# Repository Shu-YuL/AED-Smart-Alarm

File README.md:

# AED Smart Alarm

--updated Jan 17, 2023 by Shu-Yu Lin

--updated Feb 14, 2023 by Shu-Yu Lin

--updated Mar 14, 2023 by Shu-Yu Lin

--updated Mar 27, 2023 by Shu-Yu Lin

--updated Apr 4, 2023 by Shu-Yu Lin

--updated Apr 30, 2023 by Shu-Yu Lin

----------------------------------------------------------------

## Demo Video

[![Demo Video](https://lh3.googleusercontent.com/fife/APg5EOZy0qmSeqRbGbYMGeu49TxH5lmIOj3HhFyADLr6qH4S8TAaIJzbBPQnfgN_s-cPjZGFoLVAi6fIpvv_eCJc7_dvCM5OVtgkbksEu1INZQIVRCa6F0s9MO7LJb4W_VmwPlCb04PSN6UpbPwQ0xZxmr8z40CDwzgnBYsCoBz82gxHBdwRRx3AK6PTTbE4swi1r4OC8VxJj83QZSaBq_axB13bFNfvSjfkM9lRGnLXVgempMBgW_JMlQ8JZupSTVby1mXDgkiXalZTfnvae9LtgSR2kD4ZaaPTBrLYbnSjJoOcwekloa4i9upgvwhmV6UuGPqelpdEVIKUb0zCZGPnMjvvsTw_2Po14uoSeGETeqKRDd6uW2YArJD77ucuMG6qNt2Gem0yAI9NxQhCjbwBNYsCyjXGaa2BgXaY-8XdDqX1Mx07VmGnCa4fYvGSmAh2E12dP3vBXci5WtxpB1mUBuGlYkXIpvd327HO3nS2LpaJxP5piBP93a9GQkfz6OSpcxceiy6YWZIpN3cmGjMtxCaoLY8ixNX4d9ixSc4fpJpaSr7I3dkZImk0GOwjqR3xibleN_GsKG0moCss992vfX2BKf0Jc9spBMjNV6-2EfTBknmBre45v9of6kBL2GSb3d6iRzKlJ31yBRbIjqMMEWdltXHwqPHpjVWfJihoVlNe3wC1QZjWhIwFi8nv6nqt33q25jnV4J3Cq5mtlX1iGLJC8Z48cVMwxL9PpYGNN1b59B_K5U_RwdsI4gLgNnz999uuzSIeae5vx8KiVRm7SkXUUmuWnSZf90uaKBqZnekPYPGBeCjfYeUKWx3TFvJ6D0dil_QGtLUs6PXrIOAVoQ4H-kTlWyh0TMBW9p63Tly5B2JojbUkzhm8_w84FCkqoo5ElOnNsiUPa9Vcq175EdBHcfhmW7sAL8E7n9_DCXVNkeGwU5FgteWTIfNH1ESyxW_-bmufeuZ6pC-AliJgboJIaW5ZRdk58-B8PeqJ1hRr_7eFB8cpDLPJBaY8Vsg7hvgu3LZmLCbm73OjMXCEUkPtxawnfU5iJiKNJTYGJsBCpuVoUwR9EyLYlWgCaQFeHb-f_gmBUNcvSdV69-jib-mk7-MQOCFCYeSE1sNLpaVtzJmPjppp7XQHR8aCpdl6hikow4ChZ8Y4b8jt7gqkqRCYXpGSENUku35SLy19q8GuZnQ4OqCBEZjhRtRddLTxCOrBvjnOxRmyqougyYPEXUmoWOx0TKGyY6Hjho5ErniS5xrw8hKajbjSjN2OwMH83XZyLO3kg3vtkb_LYo6-RBT3pzAC8Ps_SLnvr4ILTwVZnF5t3VGGtdLRFFjI0h4WdgBgli0Bb7BPlsqJt8sOZdLPsWhUT5cgD280GumtA7FQvgNvclBMwaH1jCS99OAF7J4bOnOJqg_cTY4eNW_orggrD6oAf2BFiCVVzpNTNuUOSClDvBvviMVxwNR2MIcZnvopvAHA721Vph1cjg38kVMJq1Zw_ECSs386fh8K1YeYqixkRFTugn3-30Zh77XmVHoywLTSx9y_oey-ck5fwWFaPlW8vO2vpDeKGk-cMl2PZALwcuiQga5bR0iar3lV_XzlYYY=w1920-h1080-k-pd)](https://drive.google.com/file/d/1JeJAB9AQrucV8XEORTZ0Mz8k3fBR3jVF/view?usp=sharing "Demo video")

## Introduction

Our project aims to improve upon the current AED monitoring system used by the University of Alberta Emergency Management Team (UAEMT) and University of Alberta Protective Services (UAPS). The current system has issues with delays in receiving alerts and the need for frequent re-authentication. Our new system addresses these issues and provides more advanced notice for time-sensitive alerts, enabling UAPS to respond more quickly in case of a medical emergency.

## Method of Project Approach

Our project consists of three main components. The first component is the alarm, a monitoring device installed inside each AED cabinet and used to detect if the cabinet door opens. The second component is a base station unit installed inside the UAPS office used notify people in the office if any of the alarm monitoring devices inside the AED cabinet are triggered. The third component is a Google Apps Script managed Google Sheets, it processes HTTP requests sent from the base station and the monitoring devices and sends **an email, along	with Telegram and Discord channel announcement message** to UAPS if any of the monitoring devices are triggered.

### Monitoring Device

- Every monitoring device is powered by batteries.
- A door switch sensor is used to detect any motion of the cabinet door.
- The activation of the switch sends a digital signal to wake up and trigger the device.
- The development board used is ESP32-DevKitC V4.
- When the MCU is active, it will try to connect to campus WiFi and sends its MAC address to the Google Sheet through an HTTP GET request.
- The monitoring device will go back to sleep after it receives an acknowledgement from the Google Sheet.

### Base Station

- The base station is powered by a wall outlet power supply that will supply 5V.
- The MCU used for the base station is ESP32-WROOM-32E.
- An 2004 LCD display is mounted on the base station and connected to the MCU via the I²C interface.
- LED bulbs are used and controlled via the MCU's digital output signal. Similarly, a piezoelectric buzzer is also used and controlled via PWM signals from the MCU.
- The base station is to be connected to campus Wifi and pull data from the Google Sheet every 10 seconds through sending an HTTP GET request. It receives an empty message when no monitoring device is triggered. If any of the monitoring devices are triggered, it receives a string showing the location of this monitoring device and then activates buzzer, LED, and also displays alert message on the LCD display.
- Users can interact with the base station with onboard pushbuttons. One pushbutton labeled "Clear" is used to dismiss an alert event, while the other one is used to turn off the buzzer.

### Google Sheet

- Serves as a Web Server and online User Interface for the project
- Manages HTTP Requests and data sent from both the Base Station and the Monitoring Devices
- Provides an paired device list that can be managed by the user
- Provides an Event Log sheet that records all triggering events along with triggered date and time of each event
- Sends notifications through email, Telegram and Discord channel when an event is triggered or cleared
- Sends notifications through email, Telegram and Discord channel when a prospect low battery is detected

The project firmware is developed in C language using ESP-IDF. The Google Sheet is managed using Google Apps Script which the script is developed in JavaScript.

## Usage of this Repository

This repository contains all the code, files such as the hardware design project, PCB layout and 3D models. Please refer to the documentation for instructions on how to set up and use the system.

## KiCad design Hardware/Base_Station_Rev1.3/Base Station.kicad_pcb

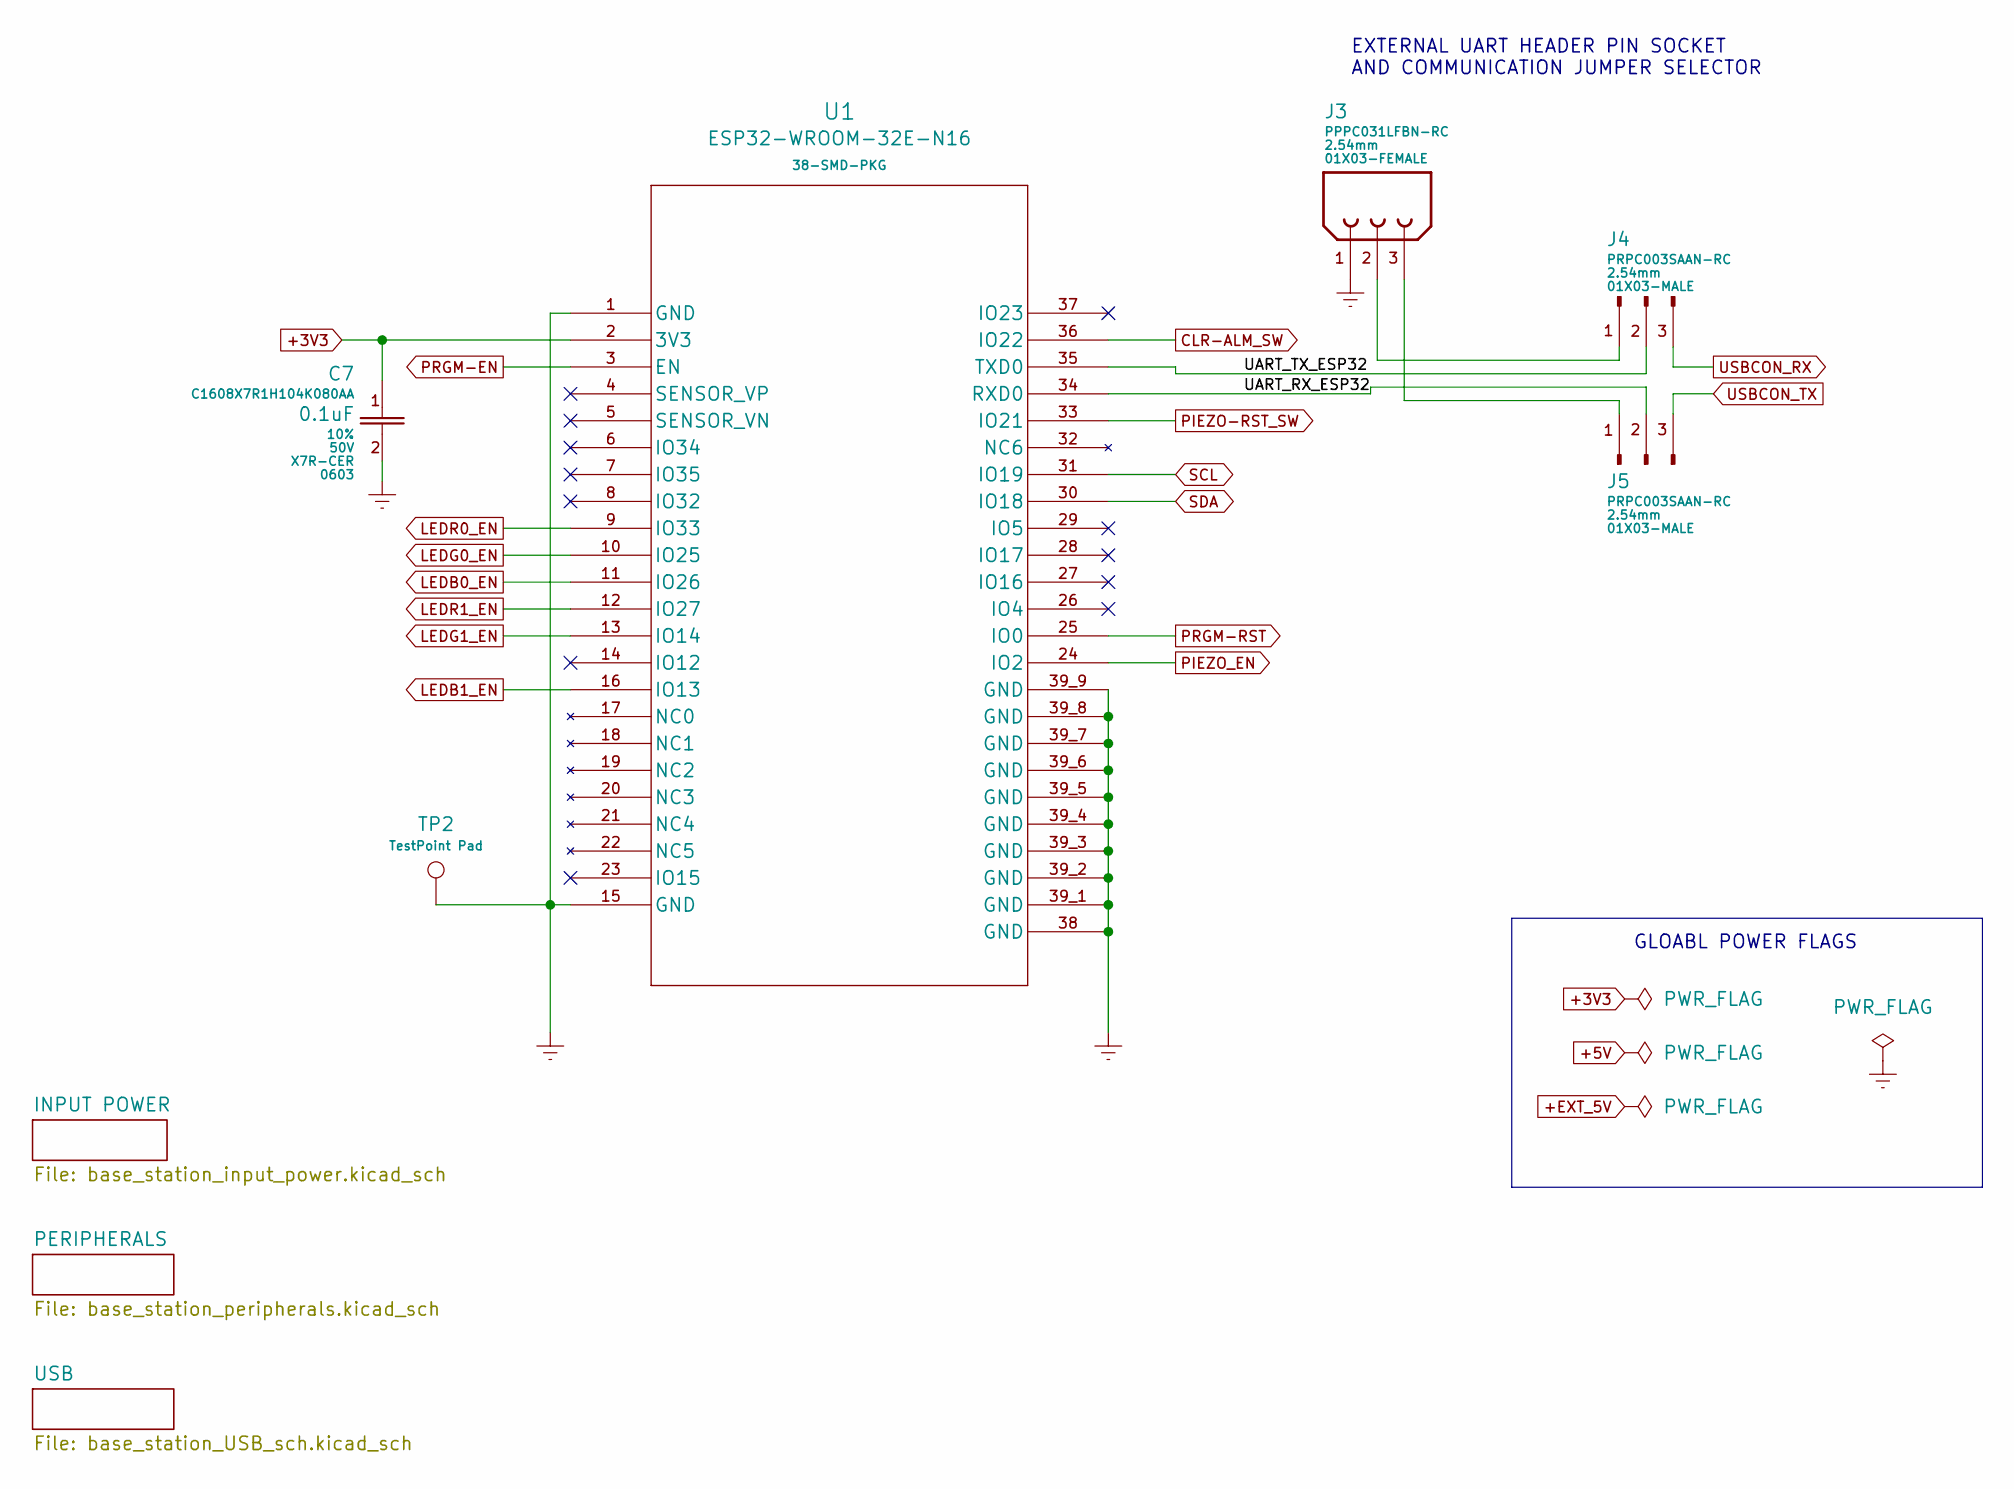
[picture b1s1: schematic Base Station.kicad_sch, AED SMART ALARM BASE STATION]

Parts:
C7: C1608X7R1H104K080AA; Tolerance 10%; Rated Voltage 50V
J3: PPPC031LFBN-RC
J4, J5: PRPC003SAAN-RC
TP2: TestPoint Pad; TestPoint_Pad_1.0x1.0mm
U1: ESP32-WROOM-32E-N16

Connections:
+3V3: C7.1, U1.2 (3V3); also elsewhere on the board
/UART_RX_ESP32: J5.2, U1.34 (RXD0)
/UART_TX_ESP32: J4.2, U1.35 (TXD0)
CLR-ALM_SW: U1.36 (IO22); also elsewhere on the board
Earth: C7.2, J3.1, TP2.1, U1.1 (GND), U1.15 (GND), U1.38 (GND), U1.39_1 (GND), U1.39_2 (GND), U1.39_3 (GND), U1.39_4 (GND), U1.39_5 (GND), U1.39_6 (GND), U1.39_7 (GND), U1.39_8 (GND), U1.39_9 (GND); also elsewhere on the board
LEDB0_EN: U1.11 (IO26); also elsewhere on the board
LEDB1_EN: U1.16 (IO13); also elsewhere on the board
LEDG0_EN: U1.10 (IO25); also elsewhere on the board
LEDG1_EN: U1.13 (IO14); also elsewhere on the board
LEDR0_EN: U1.9 (IO33); also elsewhere on the board
LEDR1_EN: U1.12 (IO27); also elsewhere on the board
unnamed: J3.2, J4.1
unnamed: J3.3, J5.1
PIEZO-RST_SW: U1.33 (IO21); also elsewhere on the board
PIEZO_EN: U1.24 (IO2); also elsewhere on the board
PRGM-EN: U1.3 (EN); also elsewhere on the board
PRGM-RST: U1.25 (IO0); also elsewhere on the board
SCL: U1.31 (IO19); also elsewhere on the board
SDA: U1.30 (IO18); also elsewhere on the board
USBCON_RX: J4.3; also elsewhere on the board
USBCON_TX: J5.3; also elsewhere on the board

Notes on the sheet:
GLOABL POWER FLAGS
EXTERNAL UART HEADER PIN SOCKET AND COMMUNICATION JUMPER SELECTOR

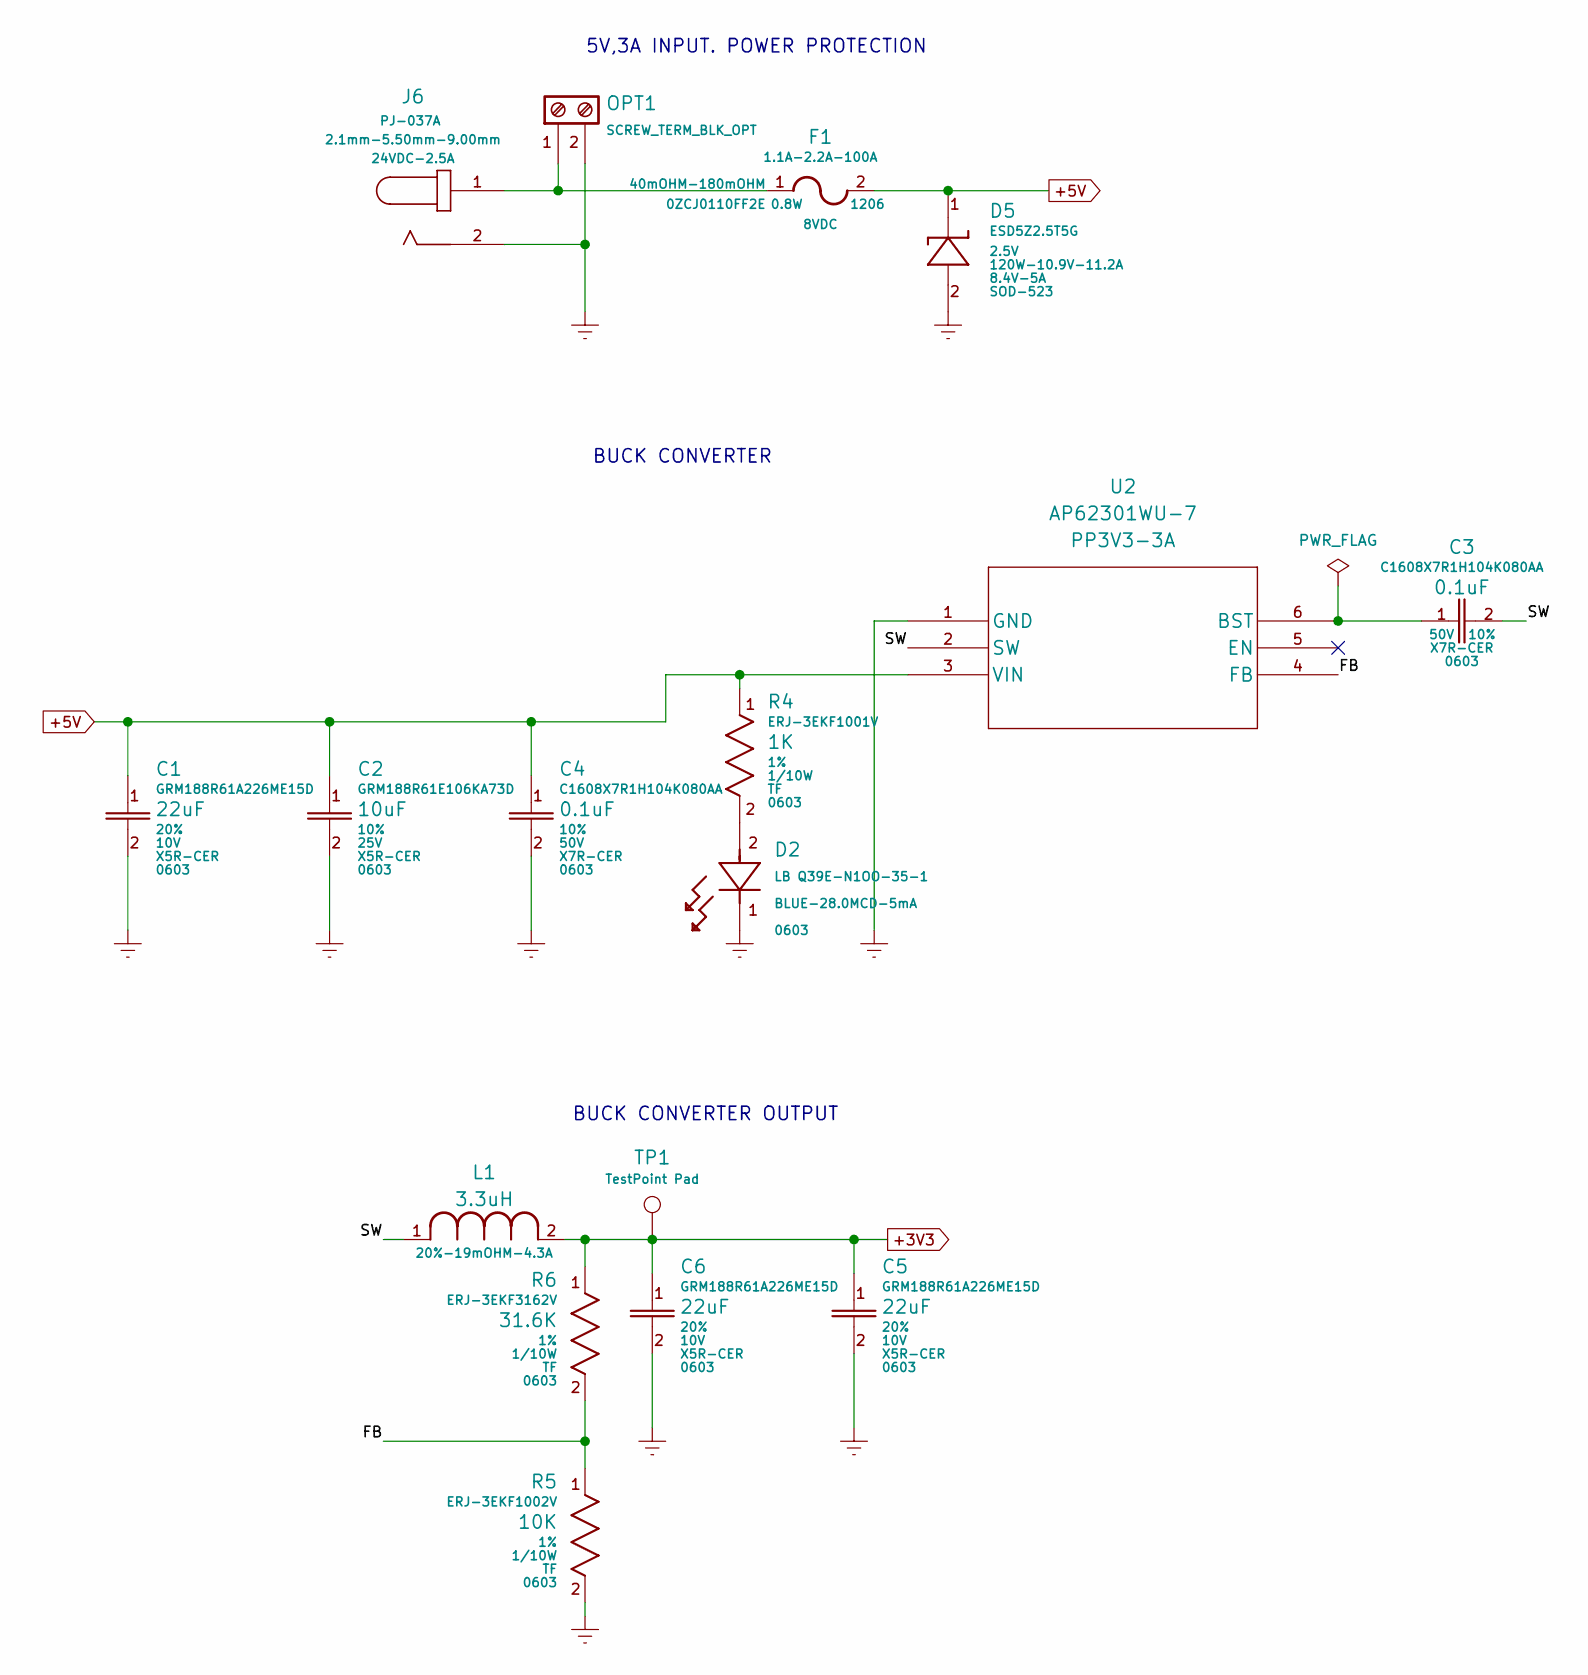
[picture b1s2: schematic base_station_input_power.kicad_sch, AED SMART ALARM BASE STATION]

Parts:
C1, C5, C6: GRM188R61A226ME15D; Tolerance 20%; Rated Voltage 10V
C2: GRM188R61E106KA73D; Tolerance 10%; Rated Voltage 25V
C3, C4: C1608X7R1H104K080AA; Tolerance 10%; Rated Voltage 50V
D2: LB Q39E-N1OO-35-1
D5: ESD5Z2.5T5G; Clamping Voltage 8.4V-5A
F1: 0ZCJ0110FF2E; Max Voltage 8VDC
J6: PJ-037A; Rating 24VDC-2.5A
L1: NRS8030T3R3MJGJ; Tolerance + DCR + Rated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 20%-19mOHM-4.3A
OPT1: SCREW_TERM_BLK_OPT; CUI_TB002-500-02BE
R4: ERJ-3EKF1001V; Tolerance 1%
R5: ERJ-3EKF1002V; Tolerance 1%
R6: ERJ-3EKF3162V; Tolerance 1%
TP1: TestPoint Pad; TestPoint_Pad_1.0x1.0mm
U2: AP62301WU-7

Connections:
+3V3: C5.1, C6.1, L1.2, R6.1, TP1.1; also elsewhere on the board
+5V: C1.1, C2.1, C4.1, D5.1 (C), F1.2, R4.1, U2.3 (VIN); also elsewhere on the board
/INPUT POWER/FB: R5.1, R6.2, U2.4 (FB)
/INPUT POWER/SW: C3.2, L1.1, U2.2 (SW)
Earth: C1.2, C2.2, C4.2, C5.2, C6.2, D2.1, D5.2 (A), J6.2, OPT1.2 (GND), R5.2, U2.1 (GND); also elsewhere on the board
unnamed: C3.1, U2.6 (BST)
unnamed: D2.2, R4.2
unnamed: F1.1, J6.1, OPT1.1 (5V)

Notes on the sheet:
BUCK CONVERTER OUTPUT
BUCK CONVERTER
5V,3A INPUT. POWER PROTECTION

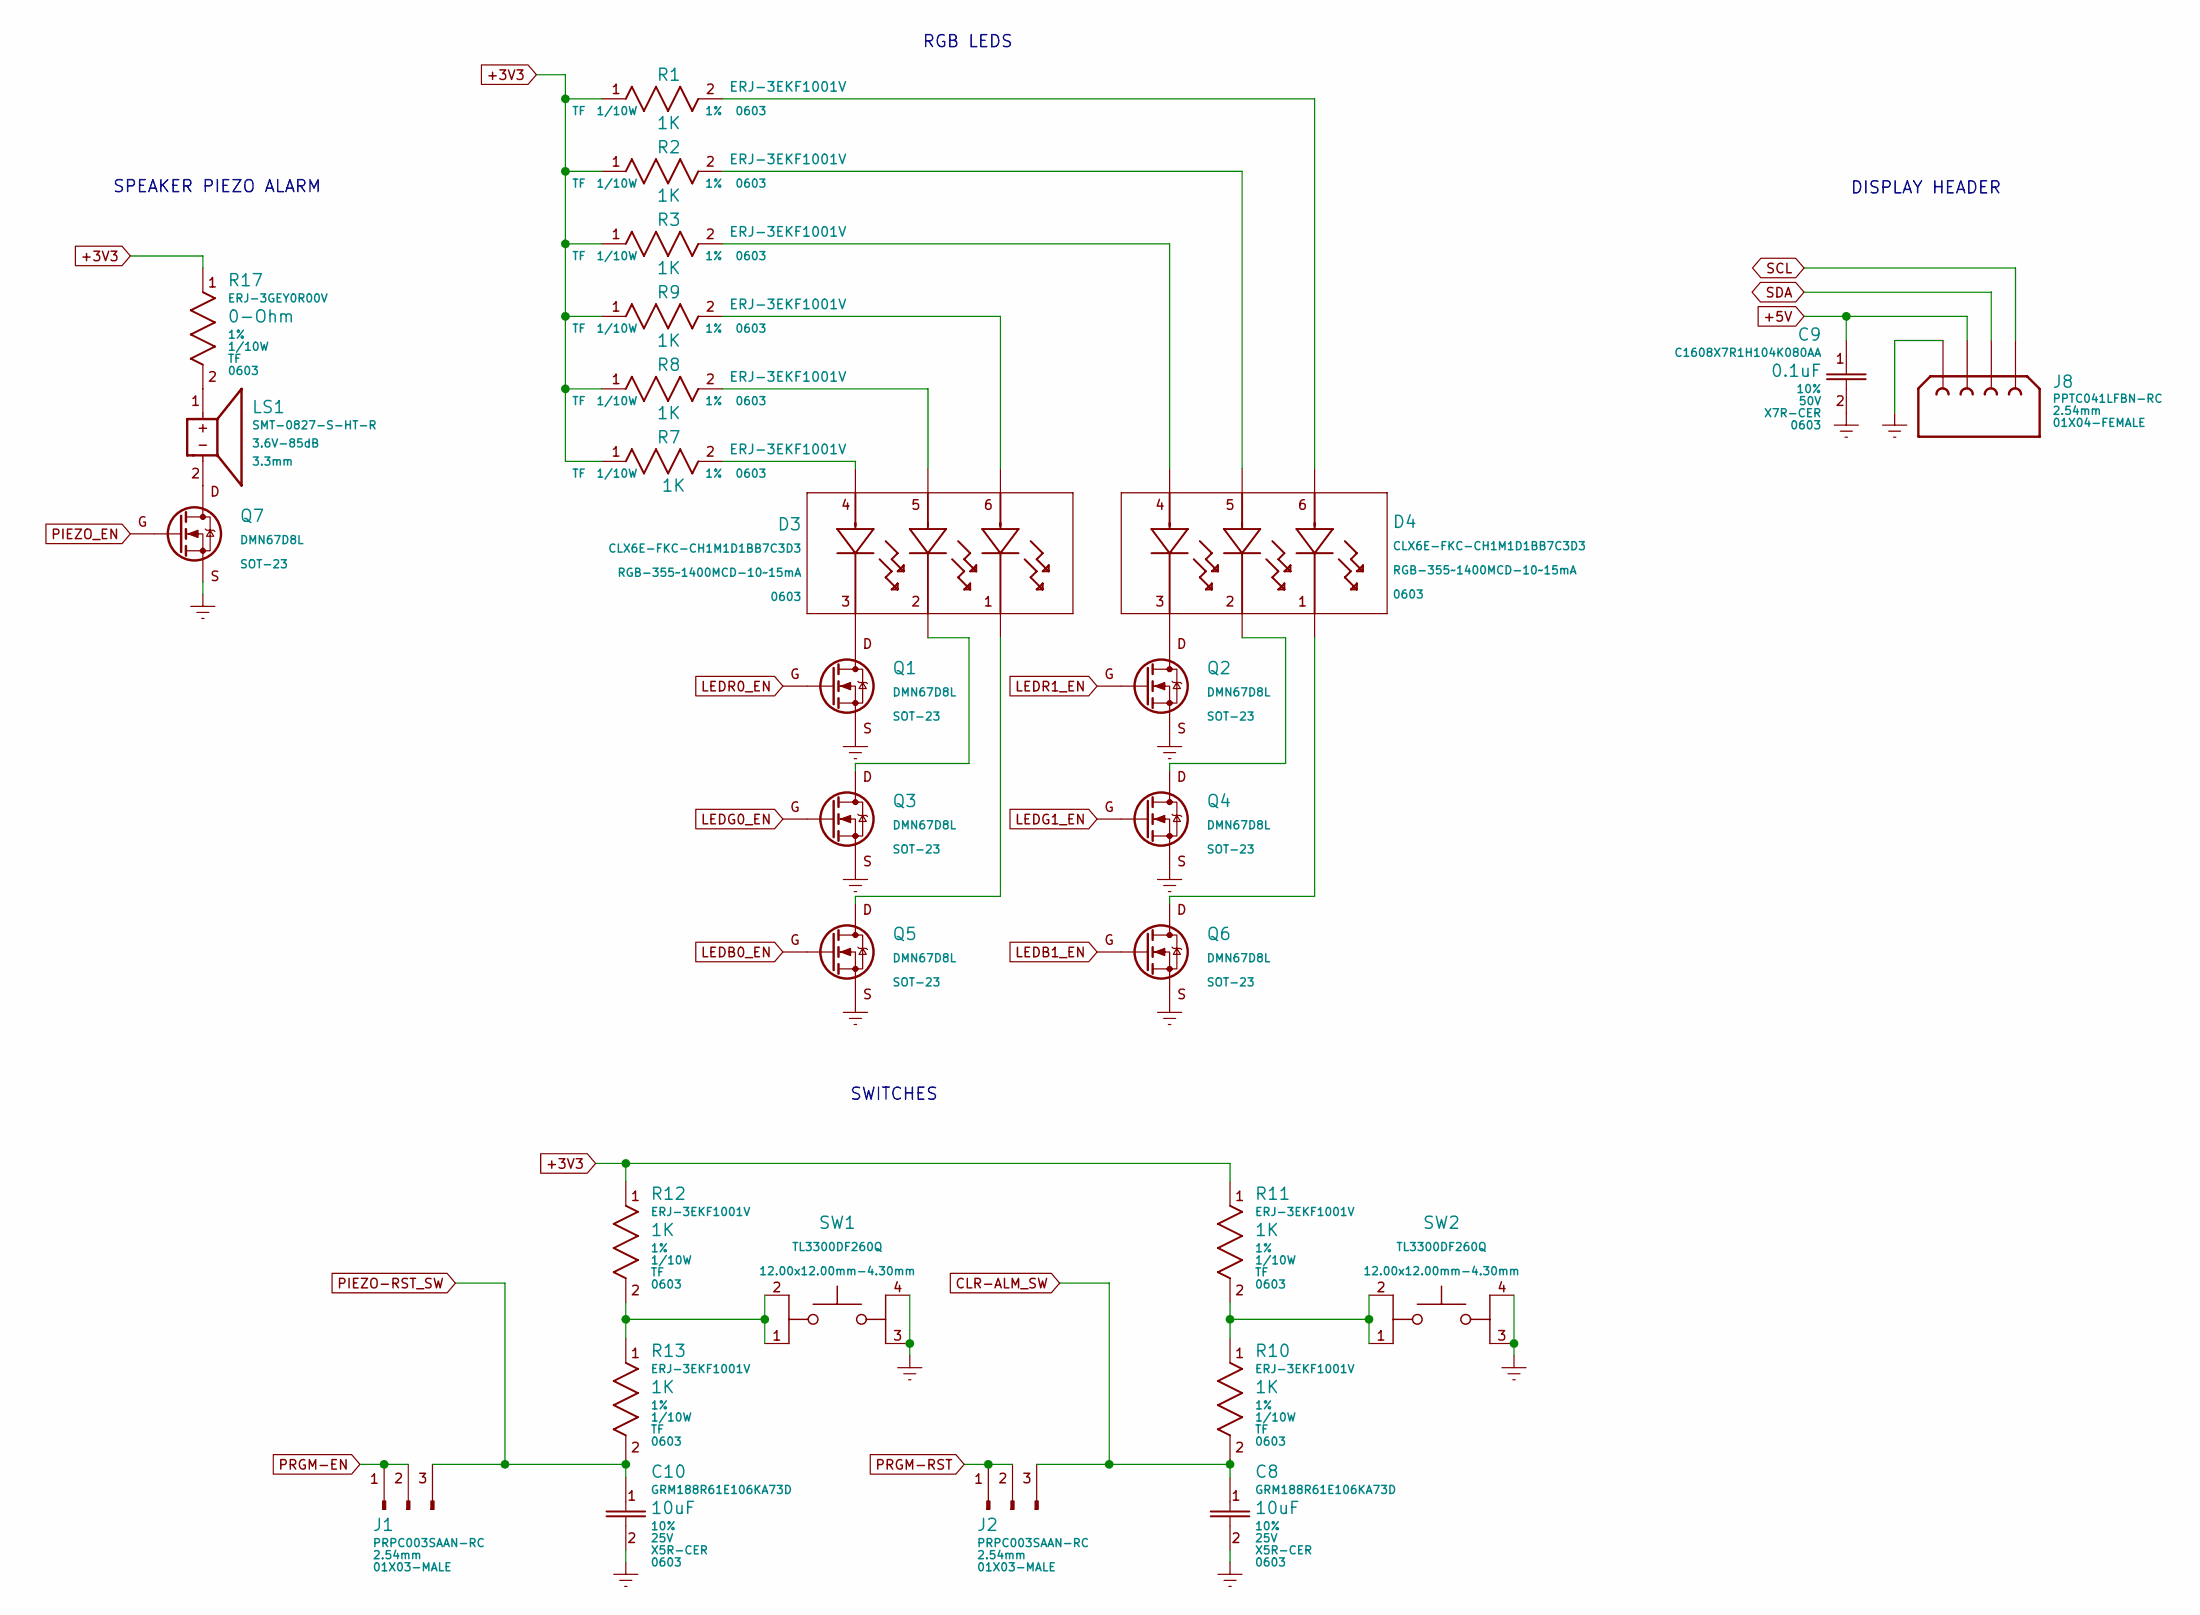
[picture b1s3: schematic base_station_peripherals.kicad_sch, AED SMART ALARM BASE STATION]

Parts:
C8, C10: GRM188R61E106KA73D; Tolerance 10%; Rated Voltage 25V
C9: C1608X7R1H104K080AA; Tolerance 10%; Rated Voltage 50V
D3, D4: CLX6E-FKC-CH1M1D1BB7C3D3
J1, J2: PRPC003SAAN-RC
J8: PPTC041LFBN-RC; PARTREV J - 04/15/2015
LS1: SMT-0827-S-HT-R; Voltage-Sound Pressure 3.6V-85dB; Part Revision 31/03/20
Q1, Q2, Q3, Q4, Q5, Q6, Q7: DMN67D8L; DMN67D8L-7
R1, R2, R3, R7, R8, R9, R10, R11, R12, R13: ERJ-3EKF1001V; Tolerance 1%
R17: ERJ-3GEY0R00V; Tolerance 1%
SW1, SW2: TL3300DF260Q; PARTREV A

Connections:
+3V3: R1.1, R2.1, R3.1, R7.1, R8.1, R9.1, R11.1, R12.1, R17.1; also elsewhere on the board
+5V: C9.1, J8.2; also elsewhere on the board
CLR-ALM_SW: C8.1, J2.3, R10.2; also elsewhere on the board
Earth: C8.2, C9.2, C10.2, J8.1, Q1.2 (S), Q2.2 (S), Q3.2 (S), Q4.2 (S), Q5.2 (S), Q6.2 (S), Q7.2 (S), SW1.3, SW1.4, SW2.3, SW2.4; also elsewhere on the board
LEDB0_EN: Q5.1 (G); also elsewhere on the board
LEDB1_EN: Q6.1 (G); also elsewhere on the board
LEDG0_EN: Q3.1 (G); also elsewhere on the board
LEDG1_EN: Q4.1 (G); also elsewhere on the board
LEDR0_EN: Q1.1 (G); also elsewhere on the board
LEDR1_EN: Q2.1 (G); also elsewhere on the board
unnamed: D3.1, Q5.3 (D)
unnamed: D3.2, Q3.3 (D)
unnamed: D3.3, Q1.3 (D)
unnamed: D3.4, R7.2
unnamed: D3.5, R8.2
unnamed: D3.6, R9.2
unnamed: D4.1, Q6.3 (D)
unnamed: D4.2, Q4.3 (D)
unnamed: D4.3, Q2.3 (D)
unnamed: D4.4, R3.2
unnamed: D4.5, R2.2
unnamed: D4.6, R1.2
unnamed: LS1.1 (+), R17.2
unnamed: LS1.2 (-), Q7.3 (D)
unnamed: R10.1, R11.2, SW2.1, SW2.2
unnamed: R12.2, R13.1, SW1.1, SW1.2
PIEZO-RST_SW: C10.1, J1.3, R13.2; also elsewhere on the board
PIEZO_EN: Q7.1 (G); also elsewhere on the board
PRGM-EN: J1.1, J1.2; also elsewhere on the board
PRGM-RST: J2.1, J2.2; also elsewhere on the board
SCL: J8.4; also elsewhere on the board
SDA: J8.3; also elsewhere on the board

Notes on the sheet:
SWITCHES
RGB LEDS
SPEAKER PIEZO ALARM
DISPLAY HEADER

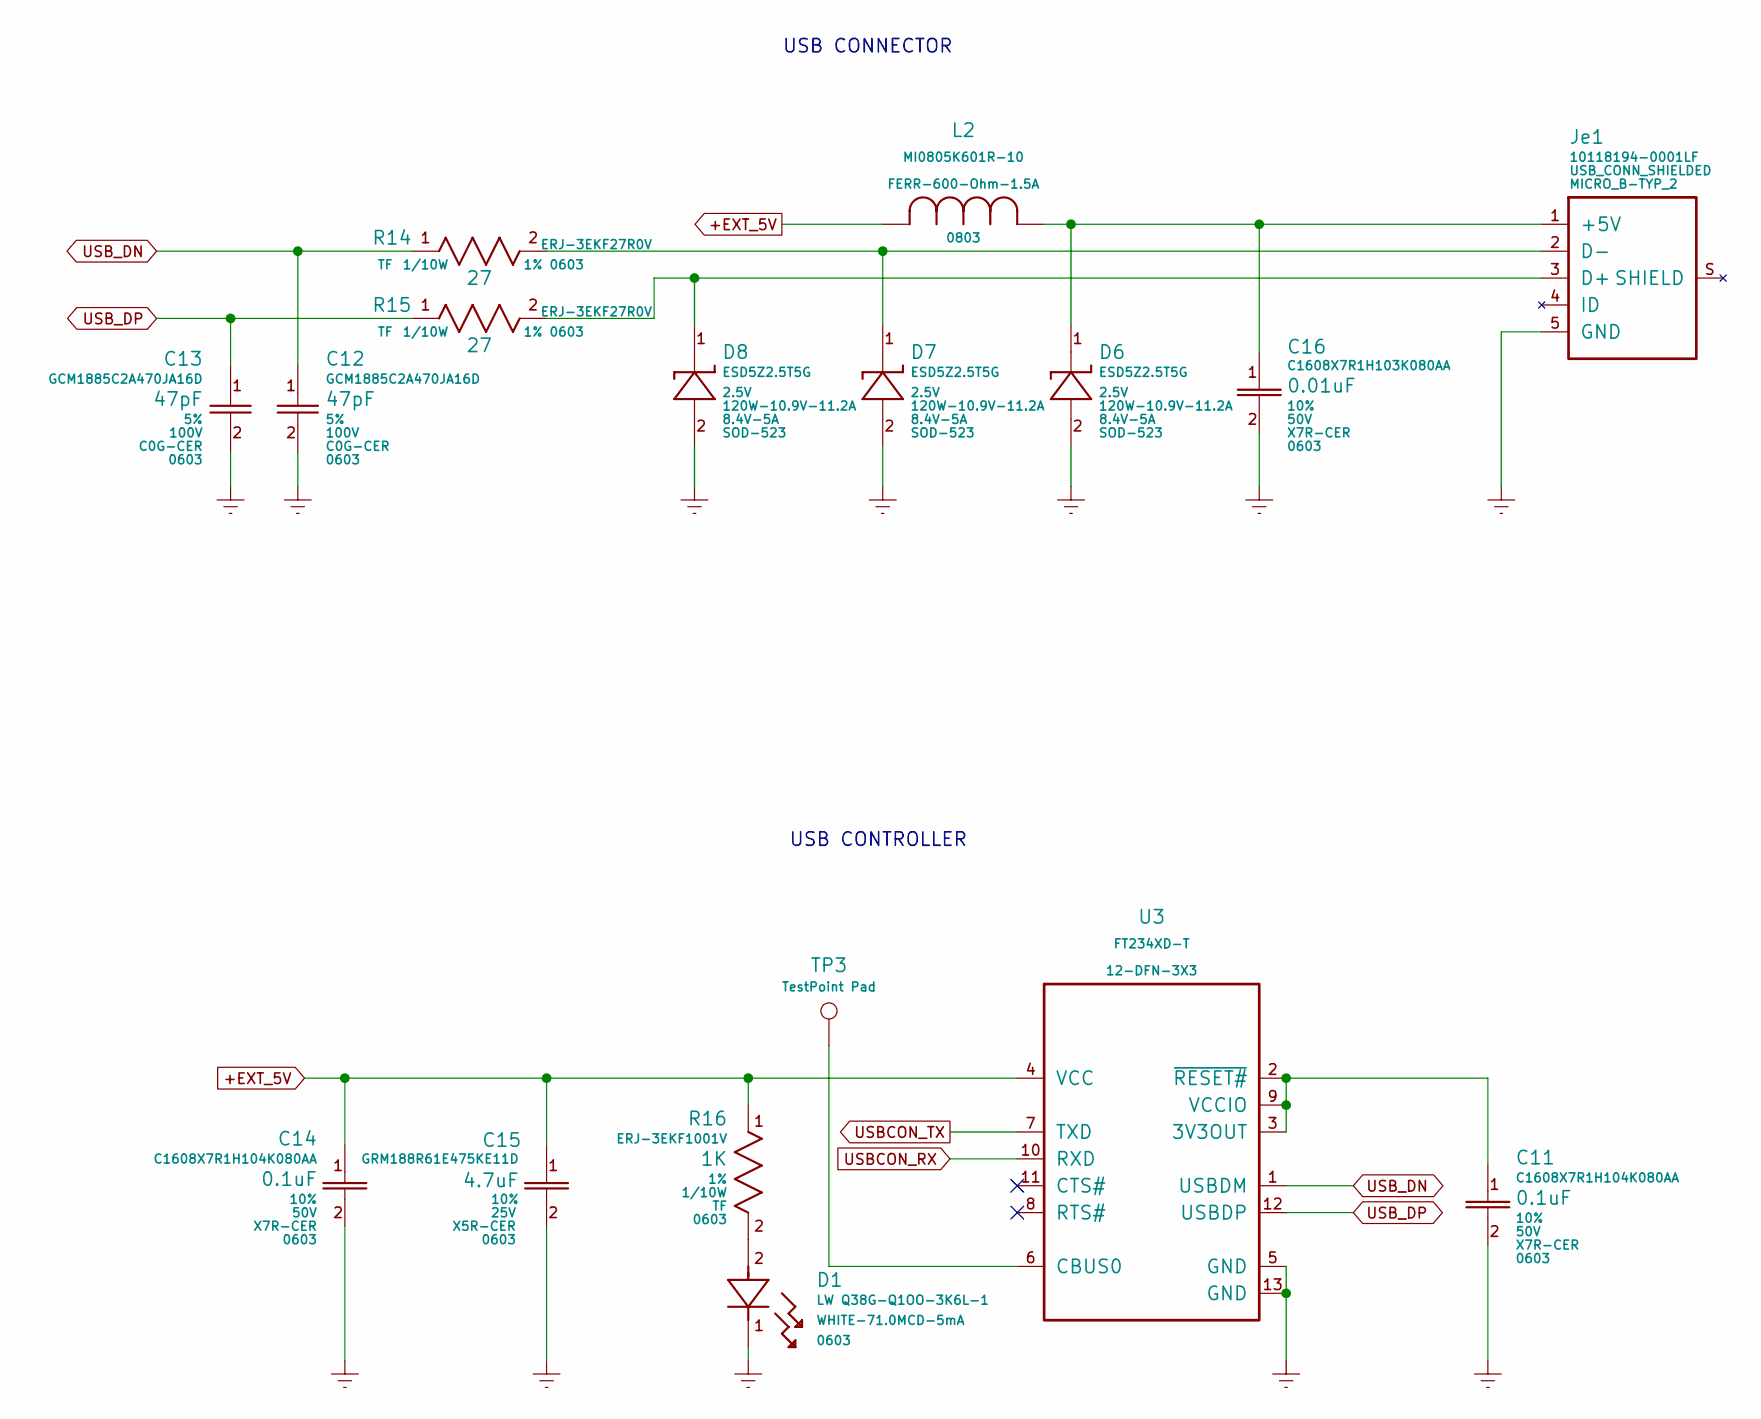
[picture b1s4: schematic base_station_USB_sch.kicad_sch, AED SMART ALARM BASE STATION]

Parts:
C11, C14: C1608X7R1H104K080AA; Tolerance 10%; Rated Voltage 50V
C12, C13: GCM1885C2A470JA16D; Tolerance 5%; Rated Voltage 100V
C15: GRM188R61E475KE11D; Tolerance 10%; Rated Voltage 25V
C16: C1608X7R1H103K080AA; Rated Voltage 50V; Tolerance 10%
D1: LW Q38G-Q1OO-3K6L-1
D6, D7, D8: ESD5Z2.5T5G; Clamping Voltage 8.4V-5A
Je1: 10118194-0001LF
L2: MI0805K601R-10
R14, R15: ERJ-3EKF27R0V; ERJ3EKF27R0V; Tolerance 1%
R16: ERJ-3EKF1001V; Tolerance 1%
TP3: TestPoint Pad; TestPoint_Pad_1.0x1.0mm
U3: FT234XD-T

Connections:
+EXT_5V: C14.1, C15.1, L2.1, R16.1, U3.4 (VCC)
Earth: C11.2, C12.2, C13.2, C14.2, C15.2, C16.2, D1.1, D6.2 (A), D7.2 (A), D8.2 (A), Je1.5 (GND), U3.5 (GND), U3.13 (GND); also elsewhere on the board
unnamed: C11.1, U3.2 (~RESET#), U3.3 (3V3OUT), U3.9 (VCCIO)
unnamed: C16.1, D6.1 (C), Je1.1 (+5V), L2.2
unnamed: D1.2, R16.2
unnamed: D7.1 (C), Je1.2 (D-), R14.2
unnamed: D8.1 (C), Je1.3 (D+), R15.2
unnamed: TP3.1, U3.6 (CBUS0)
USBCON_RX: U3.10 (RXD); also elsewhere on the board
USBCON_TX: U3.7 (TXD); also elsewhere on the board
USB_DN: C12.1, R14.1, U3.1 (USBDM)
USB_DP: C13.1, R15.1, U3.12 (USBDP)

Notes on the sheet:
USB CONTROLLER
USB CONNECTOR

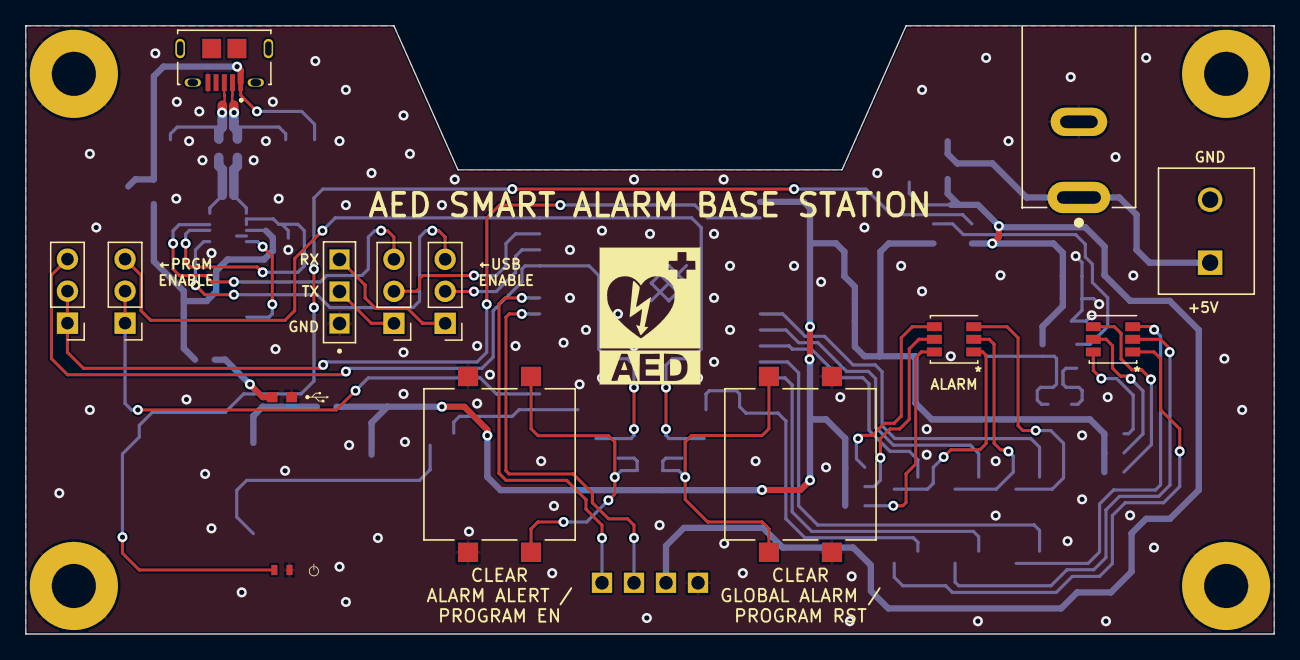
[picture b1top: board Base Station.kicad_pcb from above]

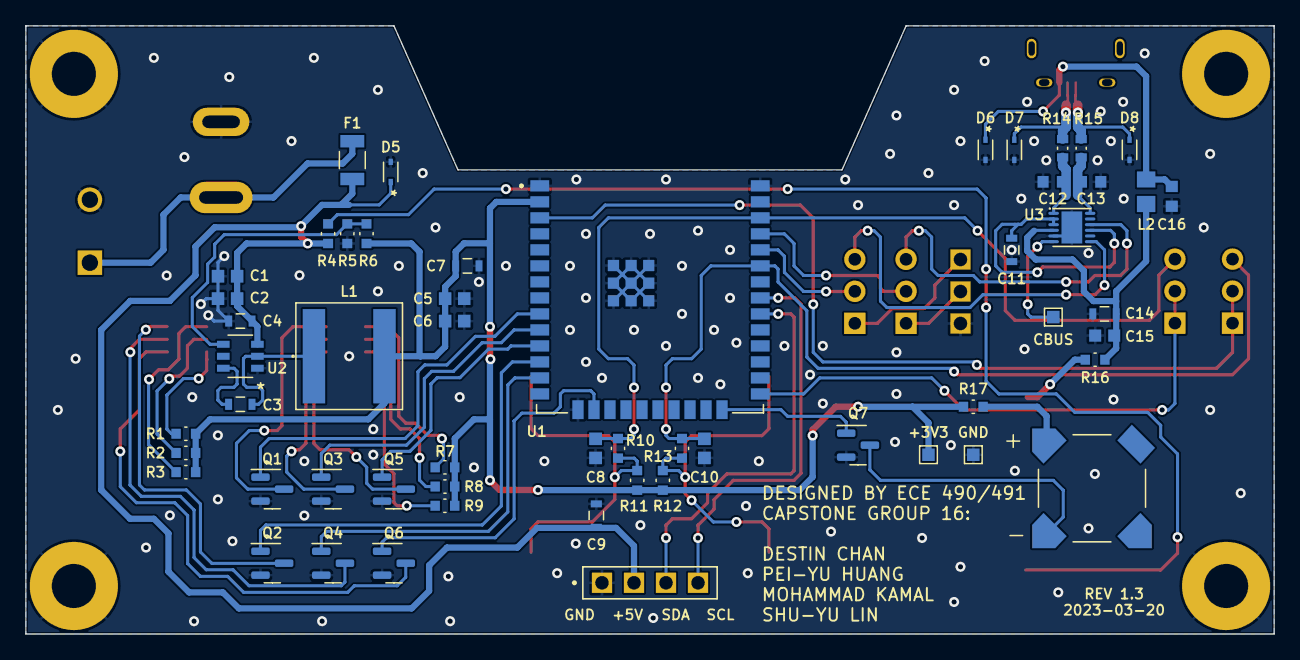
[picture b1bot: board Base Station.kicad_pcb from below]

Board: 2 copper layers, 99.1 x 48.3 mm, 69 parts (55 on the bottom side), 52 nets.

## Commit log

2023-01-12 Added sub folder
2023-01-12 Added sub folders
2023-01-17 Restore directory for the OLED code
2023-01-17 Restore directory for the base station code
2023-01-17 Remove space in folder name
2023-01-18 Update Preliminary README
2023-01-19 update oled code
2023-01-20 Modify project folder
2023-01-21 Create text
2023-01-24 integrate wifi and oled code, server code ver.0.5
2023-01-24 minor edits
2023-01-27 updated a working version with oled, wifi. Server progress 25%
2023-01-27 minor changes
2023-01-31 update a working version, server 40%
2023-02-03 Create Google_Apps_Script
2023-02-03 Update Google_Apps_Script
2023-02-03 Create Google_Apps_Script_V2
2023-02-12 Update Base station firmware
2023-02-13 update GAS url
2023-02-13 update monitoring device firmware
2023-02-14 update headers and c_cpp_properties.json files
2023-02-27 fix http client bugs and update URL. Complete MD check http response function.
2023-03-02 update a working version for the LCD, added UWS wifi code
2023-03-06 update IO pin selection, UWS function fix
2023-03-06 update MD http response checker, UWS function fix
2023-03-06 Add files via upload
    added base station peripherals
2023-03-06 Add files via upload
    Added more functions
2023-03-09 update main monitoring device code, added deep sleep
2023-03-09 update files
2023-03-09 Added CAM version Monitoring device project folder
2023-03-09 update CAM project files
2023-03-09 add test text
2023-03-09 revert edit
2023-03-09 I added this
2023-03-09 update MD_CAM project, remove UWS code
2023-03-09 remove UWS_include.h
2023-03-10 Test file deleted from project
2023-03-10 Added comments following Loren's format
2023-03-12 update: Added comments to the files related to the both monitoring devices. The wi-fi portion is left to be updated. Mo please add the comments whenever you have time.
2023-03-13 minor update on commenting
2023-03-13 update monitoring device commenting, and GS URL
2023-03-15 update BS google sheet url
2023-03-15 update README.md files
2023-03-16 update MD wake up level to low
2023-03-16 update GS url
2023-03-17 update BS buzzer code and GS URL, MD minor changes and GS URL
2023-03-17 merge
2023-03-17 remove UWS_include.h from MD ver.CAM
2023-03-26 added case 3d models
2023-03-27 update README.md files and GS URL. Added web server source code
2023-03-27 Update AED_Google_Apps_Script.js
    remove unique ID and tokens from the source code to avoid security issue
2023-03-28 update case 3D models
2023-03-28 update official GS URL
2023-03-31 update case models
2023-04-04 Added LED functionality, improved comments
2023-04-04 Added LED functionality and improved comments,
2023-04-05 update GS URL, added DevNet ssid & password
2023-04-05 Wrap up Firmware. Clean up unused files. Complete comments
2023-04-05 update official sheet URL
2023-04-05 remove kicad project
2023-04-06 fix MD bugs, update GS URL
2023-04-08 minor changes to buzzer button behavior
2023-04-10 change GS URL to the official ones
2023-04-10 modify .gitignore
2023-04-14 update MD wifi max retries

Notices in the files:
parts and their libraries:
Copyright 2021 Accelerated Designs. All rights reserved.
